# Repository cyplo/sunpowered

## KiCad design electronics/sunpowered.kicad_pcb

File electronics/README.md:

* FUSE + switch + cap ->
* 3x http://www.ti.com/lit/ds/symlink/tps55340.pdf -> 15V max 15A, SEPIC
* 
*

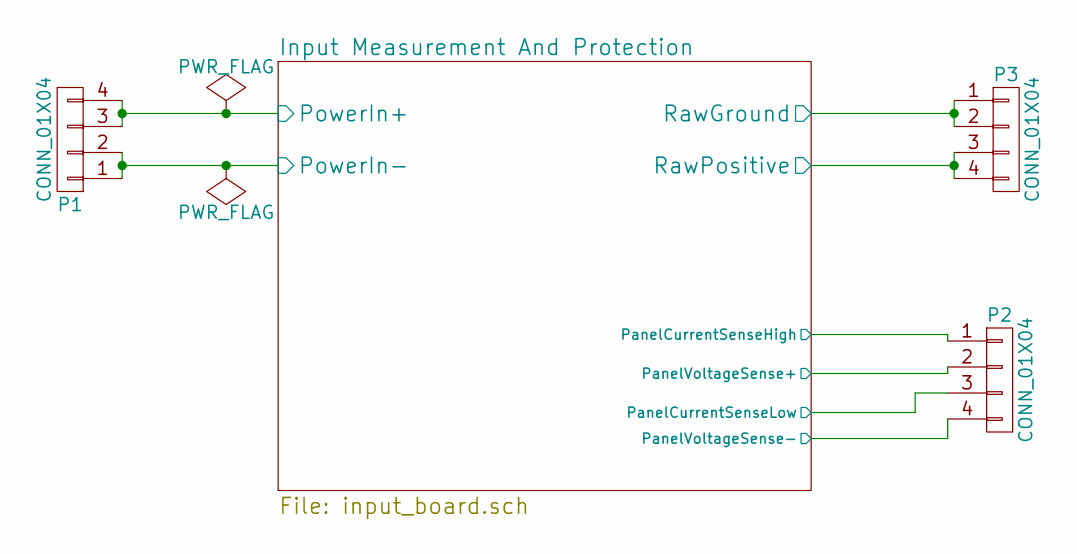
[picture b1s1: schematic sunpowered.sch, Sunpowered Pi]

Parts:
P1: CONN_01X04; AB2_TB_04_RA_5MM_L-GRN
P2: CONN_01X04; Pin_Header_Straight_1x04
P3: CONN_01X04; AB2_TB_04_RA_5MM_R-GRN

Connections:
/Input Measurement And Protection/PanelCurrentSenseHigh: P2.1, P3.1, P3.2; also elsewhere on the board
/Input Measurement And Protection/PanelCurrentSenseLow: P1.1, P1.2, P2.3, P2.4; also elsewhere on the board
/Input Measurement And Protection/PanelVoltageSense+: P1.3, P1.4, P2.2; also elsewhere on the board
/Input Measurement And Protection/RawPositive: P3.3, P3.4; also elsewhere on the board

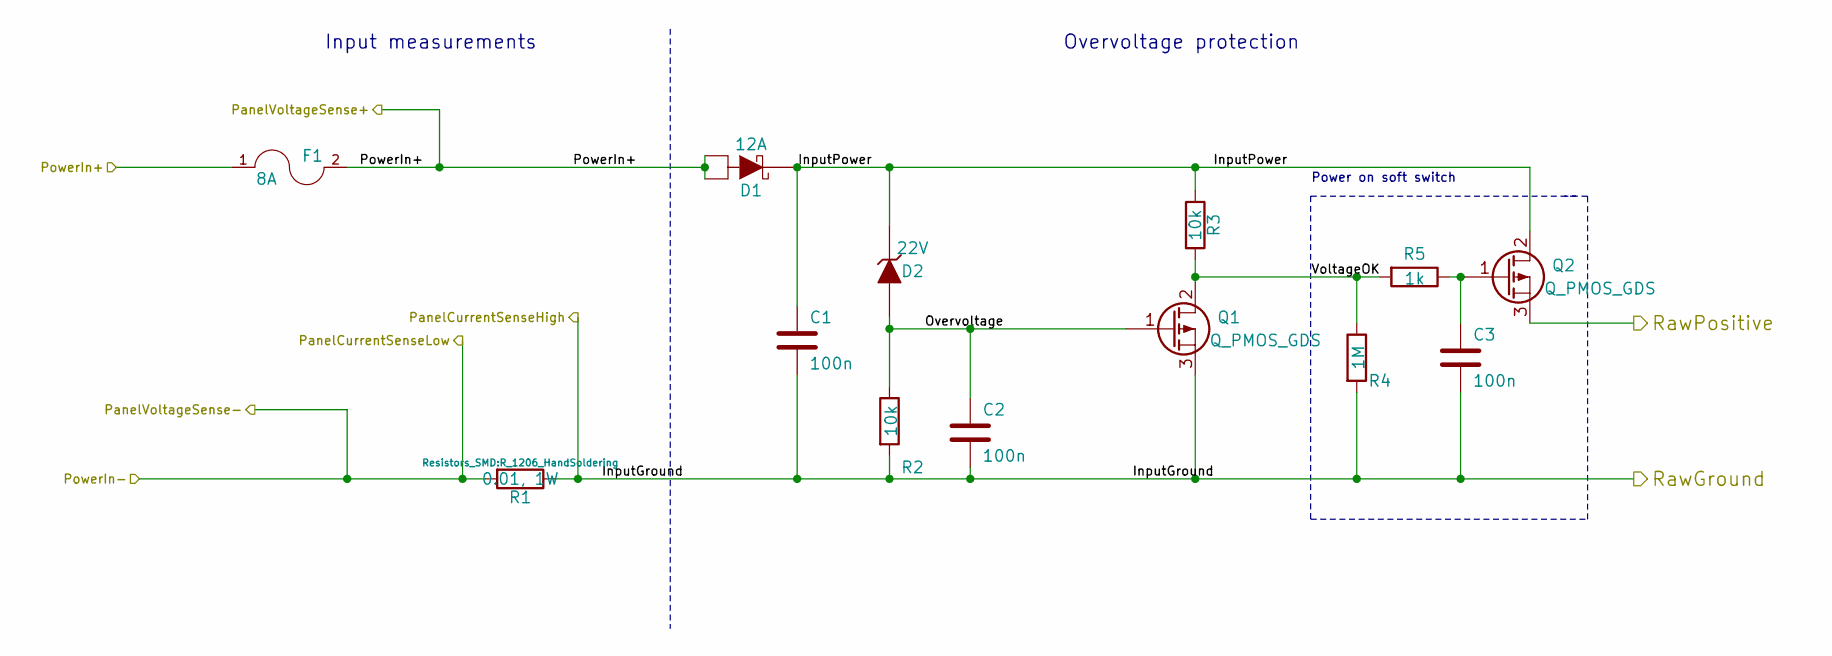
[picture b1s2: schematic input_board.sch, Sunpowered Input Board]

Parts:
C1, C2, C3: 100n; C_1206_HandSoldering
D1: 12A; TO-252-2Lead
D2: 22V; SMB_Standard
F1: 8A; Fuseholder5x20_horiz_open_universal_Type-III
Q1, Q2: Q_PMOS_GDS; D2PAK
R1: 0.01, 1W; R_1206_HandSoldering
R2: 10k; R_1206_HandSoldering
R3: 10k
R4: 1M; R_1206_HandSoldering
R5: 1k; R_1206_HandSoldering

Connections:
/Input Measurement And Protection/InputPower: C1.1, D1.2 (K), D2.1 (K), Q2.2 (D), R3.1
/Input Measurement And Protection/Overvoltage: C2.1, D2.2 (A), Q1.1 (G), R2.1
/Input Measurement And Protection/PanelCurrentSenseHigh: C1.2, C2.2, C3.2, Q1.3 (S), R1.1, R2.2, R4.2; also elsewhere on the board
/Input Measurement And Protection/PanelCurrentSenseLow: R1.2; also elsewhere on the board
/Input Measurement And Protection/PanelVoltageSense+: D1.1 (A), D1.3 (A), F1.1, F1.2; also elsewhere on the board
/Input Measurement And Protection/RawPositive: Q2.3 (S); also elsewhere on the board
/Input Measurement And Protection/VoltageOK: Q1.2 (D), R3.2, R4.1, R5.2
unnamed: C3.1, Q2.1 (G), R5.1

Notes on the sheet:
Input measurements
Power on soft switch
Overvoltage protection

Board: 2 copper layers, 15 parts (0 on the bottom side), 8 nets, no tracks yet.

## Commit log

2014-03-01 voltage and current measuring program for pi, using adc_pi
2014-03-02 different launchers, along with daemon added
2014-03-02 basic voltage plot added
2014-03-02 plotting all voltages
2014-03-02 better scaling for the plots
2014-03-09 folder path extracted to common config
2014-03-09 daemon now plots
2014-03-09 daemon now serving plots in background thread, better time interval measurements
2014-03-09 less strain on the flash storage - decouple measurement from saving
2014-03-16 fighting memory leak
2014-03-22 don't rely on number of samples to keep, purge samples older than limit instead
2014-03-29 README changes; python scripts described, with dependencies added
2014-03-29 info on how to launch as daemon
2014-07-13 time and path constants changed, more verbosity
2014-07-17 custom iamge serving class, preparing for generating image on demand
2014-07-17 on-demand plotting, to be refactored
2014-07-18 power plot added, cleaned up info box names, changed 5V rail sensor to the new one
2014-08-10 sampler extracted
2014-08-10 timekeeper extracted
2014-08-10 ambient weather temperature fetching added
2014-08-15 changed the save interval to 5 minutes
2014-12-24 moved python scripts into subfolder, to make place for non-software stuff
2014-12-24 initial notes on parts research
2015-01-03 sample output added, started working on code rework, starting from tests
2015-01-31 matplotlib now installed from pip
2015-01-31 upgraded to the new OWM version
2015-02-01 out of the process temperature data storage; works, to be refactored
2015-02-01 memory and cpu stats added
2015-02-01 script for making single measurement and uploading it to influx
2015-02-01 added network measurements; quick and dirty spike
2015-02-06 testing kicad as a tool to draw sunpowered power source
2015-02-06 git submodule with libraries added
2015-02-06 sunpowered - variable voltage input
2015-02-06 scr overvoltage protection added
2015-02-07 manual switch instead of a relay, better over voltage protection
2015-02-07 changed fuse to 8A as panels have 10A short-circuit current
2015-02-08 mosfet switch at the end of the input stage
2015-02-08 current sensor added on the front
2015-02-08 current sensor placement corrected
2015-02-08 fuse before current sensor
2015-02-08 minor wires cleanup
2015-02-08 corrected current sensor direction
2015-02-08 global in/out labels added for the input stage
2015-02-08 current and voltage sense nodes added
2015-02-08 more clear voltage sense lines
2015-02-08 current limit for current sensor chip
2015-02-08 minor cleanup
2015-02-08 mosfet power switch described
2015-02-14 README for the software section update to reflect influxdb changes
2015-02-21 power on soft-switch now features always-on capability. Added connector with all measurements
2015-02-21 flags to satisfy ERC
2015-02-21 started assigning footprints for the input protection board
2015-02-22 refreshed netlist, assigned thyristor footprint
2015-02-22 assigned footprints for most passives
2015-02-22 corrected filter cap position [lol]
2015-02-22 removed lower protection zener as it's hard to get, added footprints for the crowbar circuit components
2015-02-22 added temporary lirbary for custom footprints, to be exported to public KiCad's later
2015-02-28 all footprints added, started layout
2015-03-25 deleting the first attempt at the pcb as want to try reassigning pins first
2015-05-02 grafana dashboard export added
2015-05-02 Rename Sunpowered-1430562337569 to grafana-dashboard
2015-05-02 Newest dashboard as on data.cyplo.net
2015-05-02 fixed a bug where some measurements were shifted by a second from the others. added disk i/o measurements
2015-05-02 Added disk I/O graphs to dashboard, another cosmetic changes there
2015-05-02 Voltage stability graph added
2015-05-03 measure.py: main measurement code split into functions, still a lot to refactor there though
2015-08-25 custom footprints for semiconductors, initial auto placement on the board
2015-08-28 more clear labeling fo caps
2015-08-28 kicad library update
2015-08-28 converted to hierarchical sheets
2015-08-28 input board schematic file name correction
2015-08-28 wires that went missing after copying from sheet to sheet added
2015-08-28 ab2tech library added
2015-08-28 input baord: initial component placement
2015-09-06 Upgrade to the newest KiCad version + better caps.
    Some of the component symbols got lost while upgrading to the newest KiCad,
    recreated them.
    Calculated better filter cap values.
2015-09-06 removed 'special' library references
2015-09-06 Added 5V 3A power supply
2015-09-06 cosmetic sheet name changes
2015-11-01 input board -> mosfet in place of triak
2015-12-05 poweroff on low voltage
2015-12-13 input protection: crowbar + power on switch
2015-12-19 resigned from using hall effect current sensor
2015-12-19 redoing power supply as an 5A one
2015-12-25 migrated to 0805 for passives
2015-12-25 kicad library sync
2015-12-25 update kicad library
2015-12-25 assigning actual footprints to the input board
2015-12-25 all passives to 1206
2015-12-25 basic input board schematic finished hopefully
2015-12-25 changed power mosfets to IRFR13N20D
2015-12-25 corrected footprints for diodes
2015-12-29 overvoltage detector layout
2015-12-31 basic layout for the input board
2015-12-31 annotations on the board
2015-12-31 input board designators
2015-12-31 gerbers rename script added
2015-12-31 gerbers rename script moved to gerbers
2015-12-31 more vias for power planes
2015-12-31 new version of kicad filenames supported in gerber renamer
2015-12-31 gerbers for the board added
2015-12-31 gerber export settings added to pcb project
2016-01-01 redid gerbers with just plain KiCad export, with no renames
2016-01-02 temporarily deleting the whole library, WIP
2016-01-02 basic kicad library added with a reference to cyplo's lab server
2016-01-02 rescued old symbol for the inverter IC
2016-01-23 rescue part 2
2016-01-23 todo notes added after initial assembly
2016-01-23 changed the shutdown voltage treshold
2016-01-24 more datasheet links
2016-01-24 more TODOs after review
2016-02-06 migrate to influxdb 0.9 naively
2016-02-06 use separate measurements in influx 0.9
2016-04-17 simulated power-on soft switch - schematic only
2016-04-30 normalized component values
2017-02-05 Reference library from github instead of gitlab
